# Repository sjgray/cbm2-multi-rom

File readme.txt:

CBM-II Multi-ROM Adapter
=======================

This is an adapter for CBM-II machines. All ROM sockets including the character ROM will
take an 8K 2364 Masked ROM. 2364 ROMs are also used in other CBM products produced around
the same time. This adapter contains a PLCC socket that can hold a W27C020 EEPROM of 256K.
These EEPROMS are still available and very inexpensive so it doesn't matter if you don't
fill it up. It can erased and re-programmed over and over if needed.

You can have  up to 32 different sets of firmware/characters that are selectable
via DIP Switch with 5 switches. 

To create ROM sets you can use a utility such as my MRB - Multi-ROM Builder which will let
you drag-and-drop and arranges however you like, then build a binary image that can be
written to the EEPROM. I used a TL-866 programmer along with a 32-pin PLCC to DIP adapter
to program the W27C010.

BOM
===

As 5-switch DIP SWITCH versions are not as common you can also install a 6-switch if you
have one. You can also install any lesser number switch if you don't need all 32 slots.
If you only need one slot you can leave off the switch entirely as the resistor-pack will
keep the lines grounded automatically. Finally, you could wire up individual SPST switches
and mount them remotely.

The design uses a 5-pin resistor pack (4 resistors) to be able to fit between the DIP pins.
You need to install a separate resistor for the 5th switch.

You should use round machined-pin headers so as not to damage the sockets on the CBM-II
motherboard.

Gerbers
=======

Gerbers are available in the \gerbers folder. You can simply send the ZIP file to your
favorite pcb manufacturer. I generally use JLCPCB and have had no quality issues with them.

History
=======

* V1.0 created 2025-06-03. Tested and working as expected.

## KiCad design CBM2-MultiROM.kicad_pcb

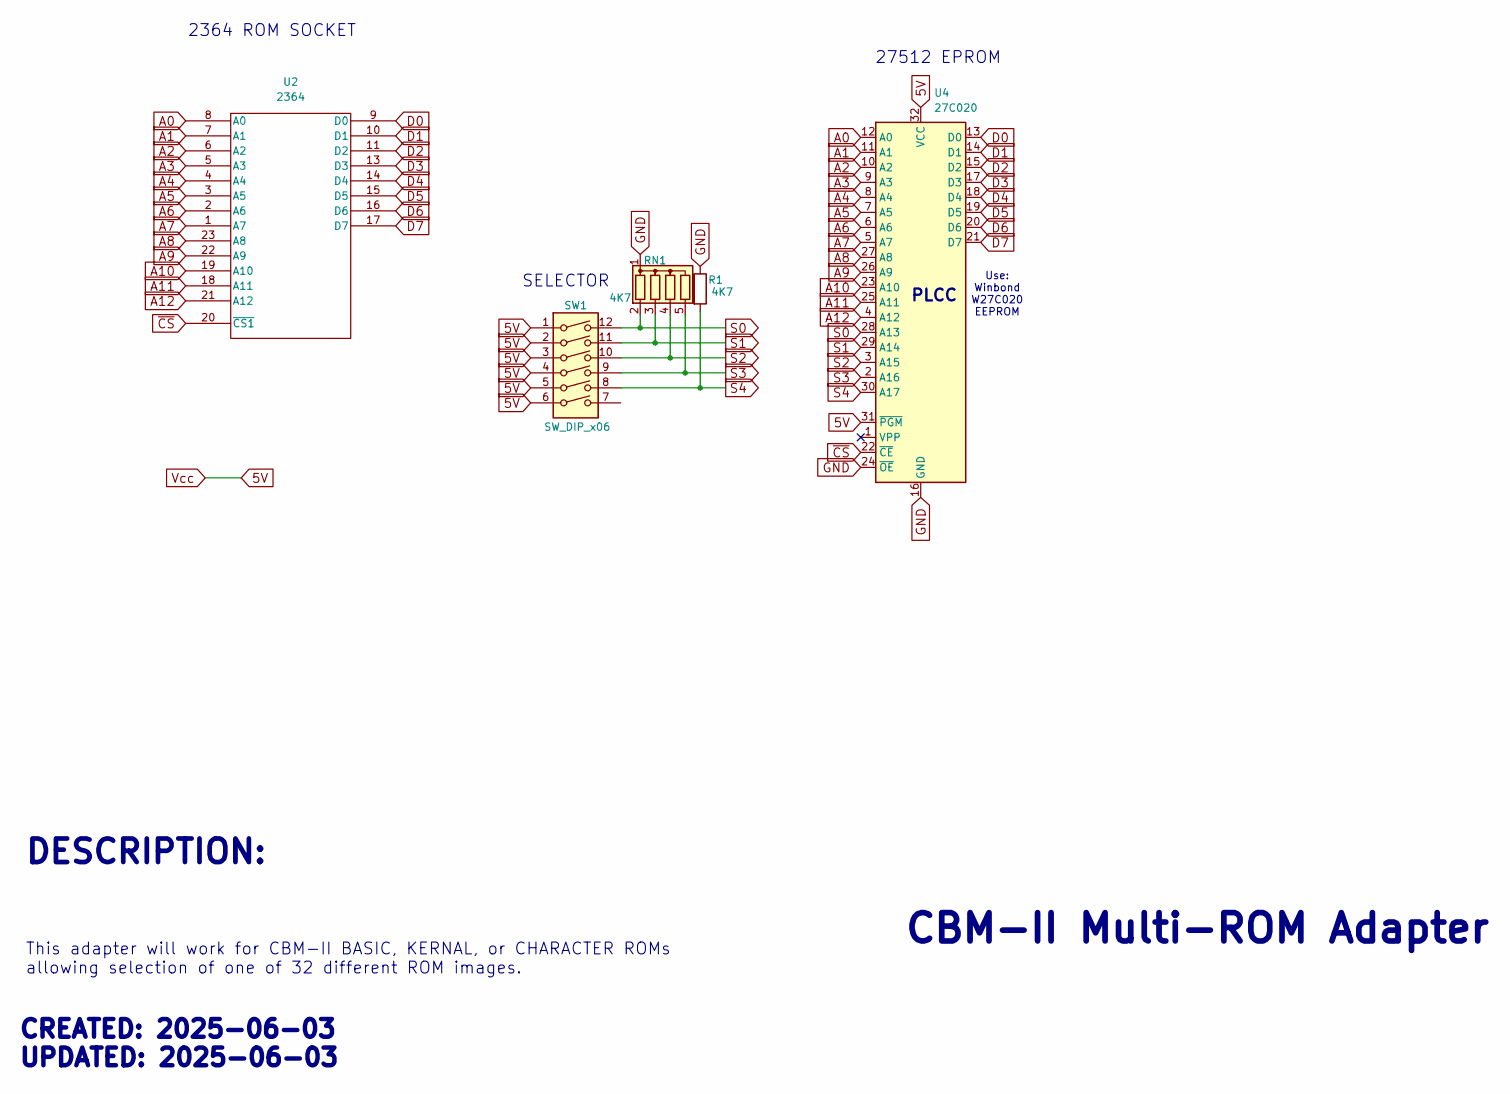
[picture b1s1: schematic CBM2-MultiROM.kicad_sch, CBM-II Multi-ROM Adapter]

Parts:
R1: 4K7; R_Axial_DIN0204_L3.6mm_D1.6mm_P5.08mm_Horizontal
RN1: 4K7; R_Array_SIP5
SW1: SW_DIP_x06; SW_DIP_SPSTx06_Slide_6.7x16.8mm_W7.62mm_P2.54mm_LowProfile
U2: 2364; DIP-24_W15.24mm_Socket
U4: 27C020; PLCC-32_THT-Socket

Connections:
5V: SW1.1, SW1.2, SW1.3, SW1.4, SW1.5, SW1.6, U2.24 (Vcc), U4.31 (~PGM), U4.32 (VCC)
A0: U2.8 (A0), U4.12 (A0)
A1: U2.7 (A1), U4.11 (A1)
A2: U2.6 (A2), U4.10 (A2)
A3: U2.5 (A3), U4.9 (A3)
A4: U2.4 (A4), U4.8 (A4)
A5: U2.3 (A5), U4.7 (A5)
A6: U2.2 (A6), U4.6 (A6)
A7: U2.1 (A7), U4.5 (A7)
A8: U2.23 (A8), U4.27 (A8)
A9: U2.22 (A9), U4.26 (A9)
A10: U2.19 (A10), U4.23 (A10)
A11: U2.18 (A11), U4.25 (A11)
A12: U2.21 (A12), U4.4 (A12)
D0: U2.9 (D0), U4.13 (D0)
D1: U2.10 (D1), U4.14 (D1)
D2: U2.11 (D2), U4.15 (D2)
D3: U2.13 (D3), U4.17 (D3)
D4: U2.14 (D4), U4.18 (D4)
D5: U2.15 (D5), U4.19 (D5)
D6: U2.16 (D6), U4.20 (D6)
D7: U2.17 (D7), U4.21 (D7)
GND: R1.1, RN1.1 (common), U2.12 (GND), U4.16 (GND), U4.24 (~OE)
S0: RN1.2 (R1), SW1.12, U4.28 (A13)
S1: RN1.3 (R2), SW1.11, U4.29 (A14)
S2: RN1.4 (R3), SW1.10, U4.3 (A15)
S3: RN1.5 (R4), SW1.9, U4.2 (A16)
S4: R1.2, SW1.8, U4.30 (A17)
~CS: U2.20 (~CS1), U4.22 (~CE)

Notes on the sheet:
CREATED: 2025-06-03 UPDATED: 2025-06-03
This adapter will work for CBM-II BASIC, KERNAL, or CHARACTER ROMs allowing selection of one of 32 different ROM images.
2364 ROM SOCKET
PLCC
Use: Winbond W27C020 EEPROM
27512 EPROM
SELECTOR
DESCRIPTION:
CBM-II Multi-ROM Adapter

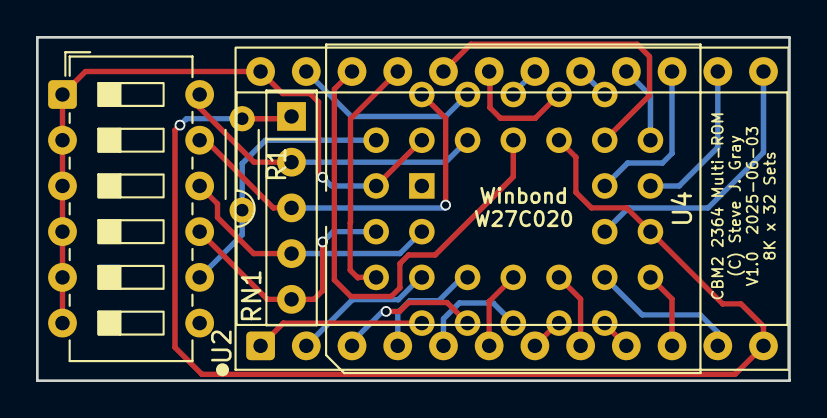
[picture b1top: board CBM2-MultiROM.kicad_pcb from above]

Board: 2 copper layers, 41.8 x 19.1 mm, 5 parts (0 on the bottom side), 29 nets.

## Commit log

2025-06-17 V1.0 adapter Kicad files and Gerbers
    This version has been successfully tested in a CBM-II High-profile machine but should work without any issues on LP machines and the P500.
2025-08-13 Fix some typos in README
    oops
